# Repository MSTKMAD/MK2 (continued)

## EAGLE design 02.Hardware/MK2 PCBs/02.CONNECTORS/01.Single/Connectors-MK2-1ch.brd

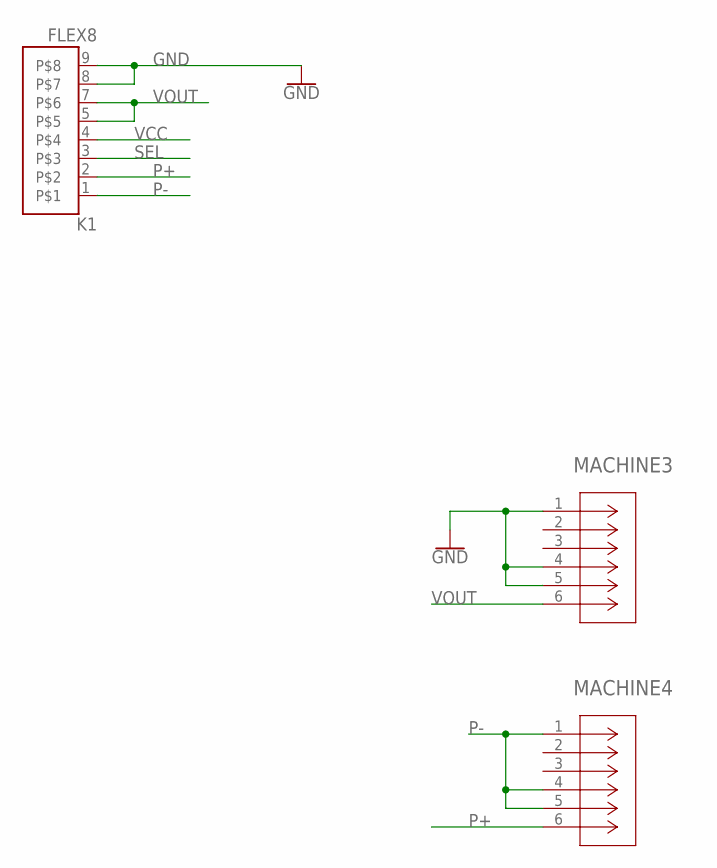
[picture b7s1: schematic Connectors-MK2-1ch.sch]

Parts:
K1: FLEX8
MACHINE3, MACHINE4: ACJS-MHDR; CONN_MHDR_AMP

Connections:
GND: K1.8, K1.9, MACHINE3.1, MACHINE3.4, MACHINE3.5
P+: K1.2, MACHINE4.6
P-: K1.1, MACHINE4.1, MACHINE4.4, MACHINE4.5
SEL: K1.3
VCC: K1.4
VOUT: K1.5, K1.7, MACHINE3.6

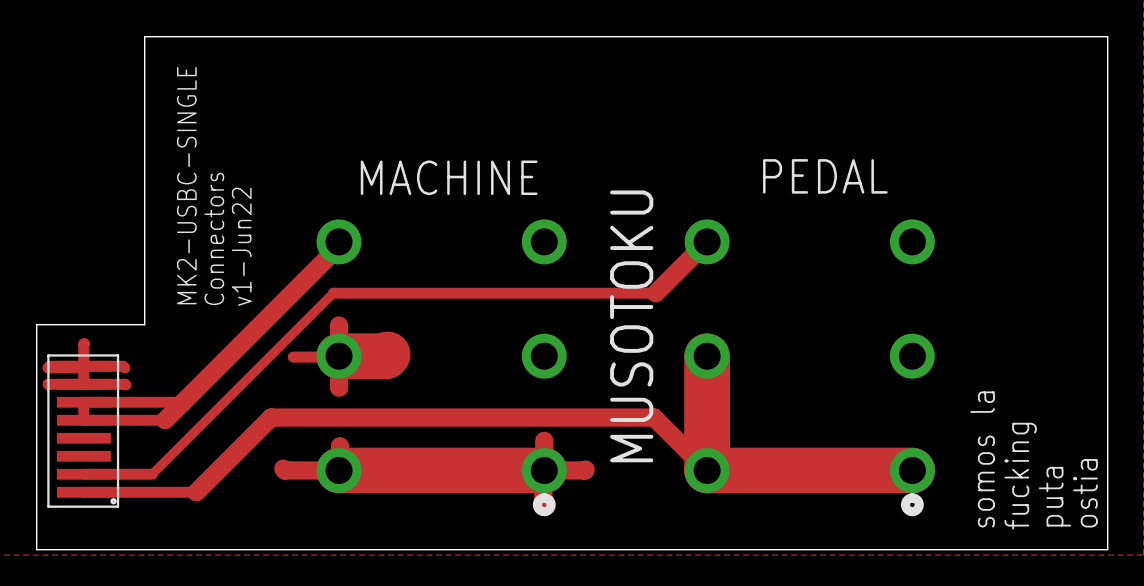
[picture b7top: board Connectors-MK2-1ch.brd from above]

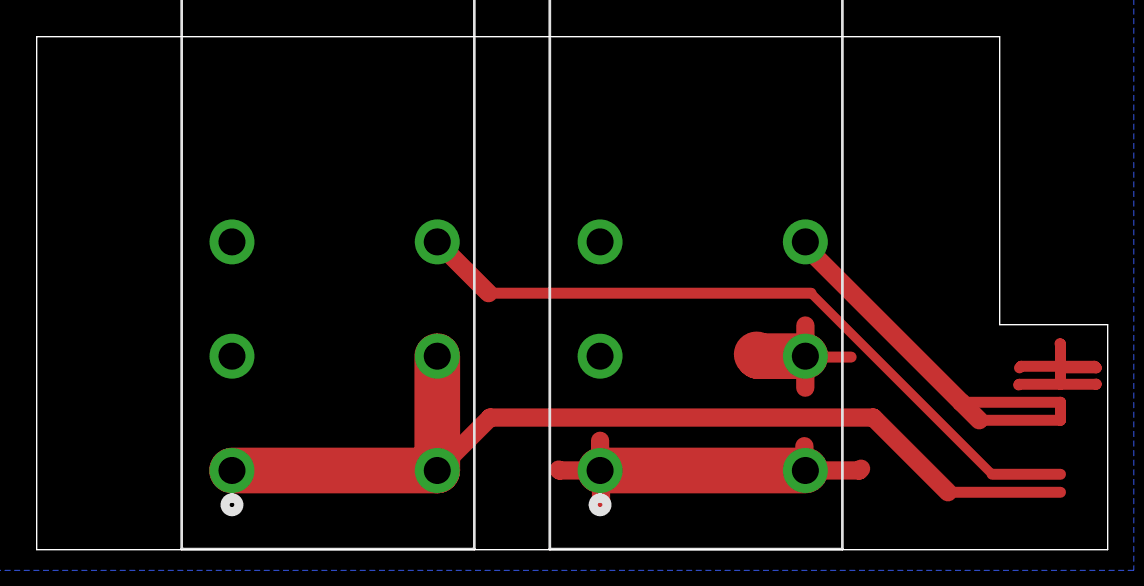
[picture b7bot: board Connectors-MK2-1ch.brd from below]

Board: 2 copper layers, 59.5 x 28.5 mm, 3 parts (2 on the bottom side), 4 nets.

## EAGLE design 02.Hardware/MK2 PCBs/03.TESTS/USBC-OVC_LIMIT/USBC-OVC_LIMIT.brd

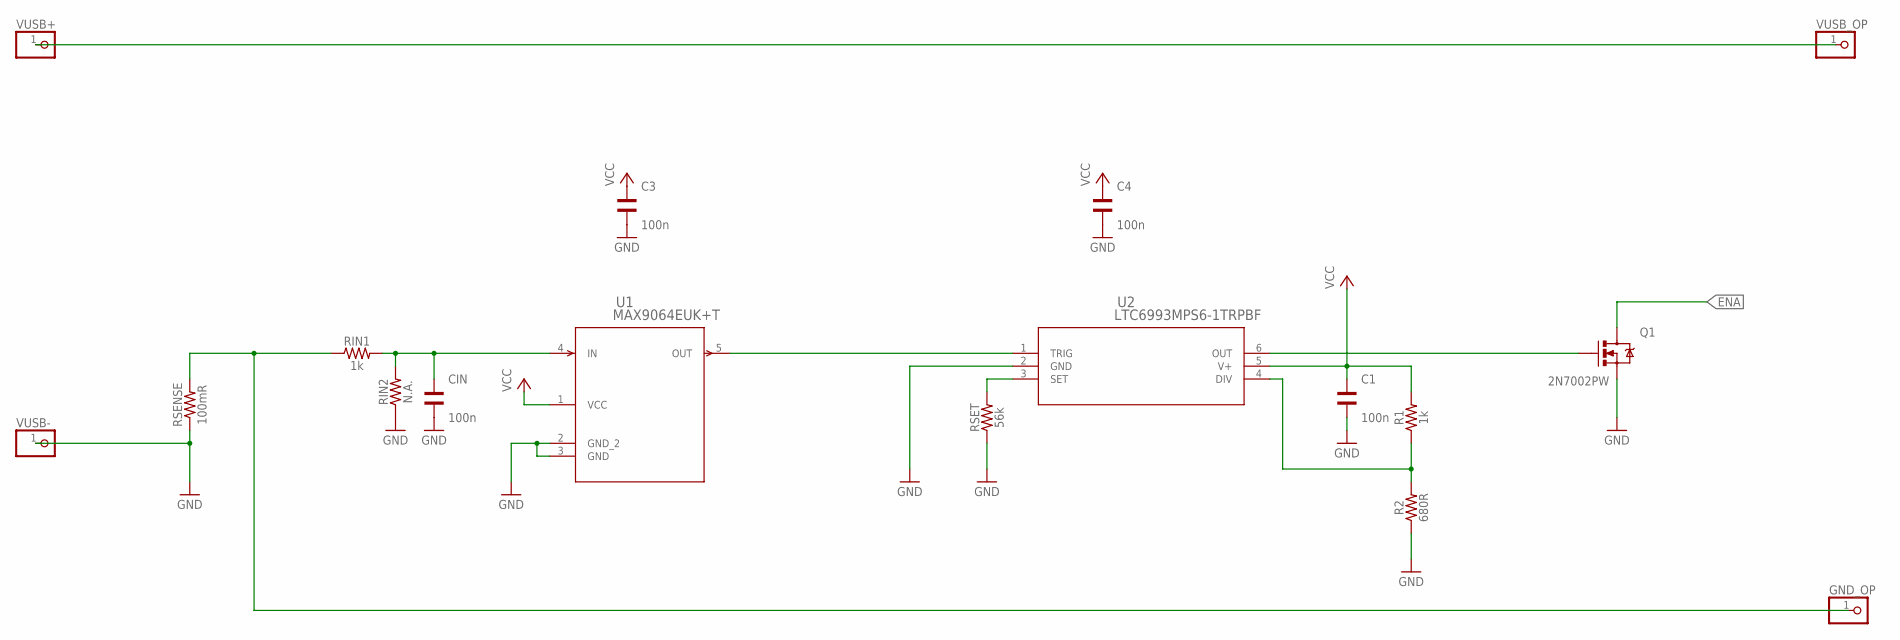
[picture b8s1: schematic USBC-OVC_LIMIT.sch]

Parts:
C1, C3, C4: 100n; WCAP-CSGP_1206
CIN: 100n; WCAP-CSGP_1206
GND_OP: PINHD-1X1; 1X01
Q1: 2N7002PW; SOT323
R1: 1k; 1206
R2: 680R; 1206
RIN1: 1k; 1206
RIN2: N.A.; 1206
RSENSE: 100mR; 1206
RSET: 56k; 1206
U1: MAX9064EUK+T; 21-0057F_MXM
U2: LTC6993MPS6-1TRPBF; TSOT-23_S6_LIT
VUSB+: PINHD-1X1; 1X01
VUSB-: PINHD-1X1; 1X01
VUSB_OP: PINHD-1X1; 1X01

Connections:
ENA: Q1.3 (D)
GND: C1.1, C3.1, C4.1, CIN.1, Q1.2 (S), R2.1, RIN2.1, RSENSE.1, RSET.1, U1.2 (GND_2), U1.3 (GND), U2.2 (GND), VUSB-.1
GND_OP: GND_OP.1, RIN1.1, RSENSE.2
unnamed: RSET.2, U2.3 (SET)
unnamed: CIN.2, RIN1.2, RIN2.2, U1.4 (IN)
unnamed: R1.1, R2.2, U2.4 (DIV)
unnamed: Q1.1 (G), U2.6 (OUT)
unnamed: U1.5 (OUT), U2.1 (TRIG)
VCC: C1.2, C3.2, C4.2, R1.2, U1.1 (VCC), U2.5 (V+)
VUSB_OP: VUSB+.1, VUSB_OP.1

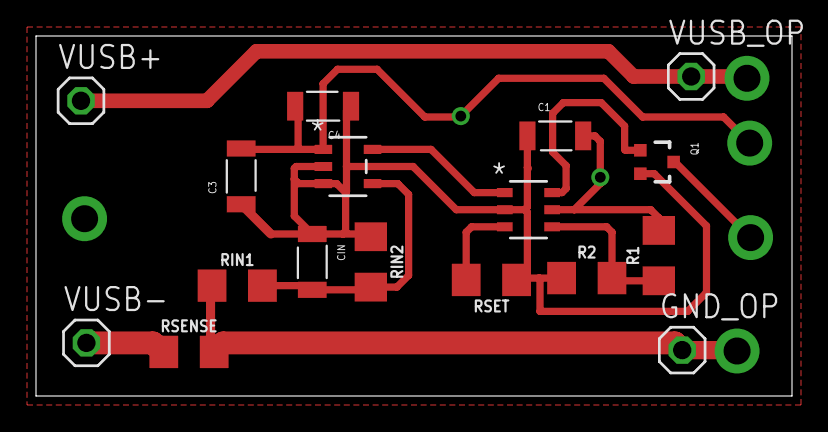
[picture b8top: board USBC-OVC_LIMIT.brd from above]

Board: 2 copper layers, 42.0 x 20.0 mm, 17 parts (0 on the bottom side), 9 nets.

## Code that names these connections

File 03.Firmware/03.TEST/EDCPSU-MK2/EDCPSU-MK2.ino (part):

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const int OVC_UVOLT_MAX_TIME = 1000;          // Maximum time that can last the overcurrent with the UNDERVOLTAGE method (Milliseconds)
const unsigned int OVC_SENSE_LIMIT_INF = 760; // Current limit above which it is still considered an overcurrent sense situation 2.6A
const unsigned int OVC_SENSE_LIMIT_SUP = 800; // Current limit above which it is Triggered the overcurrent sense situation 2.7A real (in theory this value should trigger at 3.1A but Rsense is contaminated by a trace track to the amplifier)
const byte MAX_OVC_ERRORS = 5;                // Max number of OVC errors per session in order to request the release of the PEDAL to the user
const int UNDERVOLT_1V5 = 100;                // Sensed voltage corresponding to 2V for undervoltage sensing
const int UNDERVOLT_1V8 = 121;                // Sensed voltage corresponding to 1.8V for undervoltage sensing
const float DISP_TO_VTARGET_CONV = 5.2;       // Conversion factor to get display values into same scale as VoutSense values (1/19.6)*1023 = 52.2 --> to DISP 52/10=5.2
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const unsigned long RX_CHAR_TIMEOUT = 10; // (ms) time allowed for an orphan char received via Serial
const byte TLG_RX_BYTES = 3;              // Bytes compounding a Serial telegram of the Test mode

const byte ALARM_FLAG = 0; // Flag to report that OVC_ALARM sensor is activated. This is set in ReportFlags report byte in the Test Mode
const byte PEDAL_FLAG = 1; // Flag to report that PEDAL input is activated. This is set in ReportFlags report byte in the Test Mode
// ------------------------------------------------- PIN DEFINITION r7,r6 -------------------------------------------
const int DCDC_EN = A1; //
//const int LED_FRONT = 9; // Arduino 7 (pin 11 in ATMEGA368)
const int LIFE_CHECK = 9; // SPARE2 Pin used for testing

const int ISEN = A7;
const int VOSEN = A6;
const int PUSHBUTTON_IP = A2; // HIGH = OFF; LOW = ON
const int ROTPUSH_IP = A3;    // HIGH = OFF; LOW = ON
const int ROTA = 4;
const int OVC_ALARM = 5; // New in r8.0 (before pin 2)
const int ROTB = 3;
const int BUZZ = 6;
const int PEDAL_IP = 2;    // New in r8.0 (before pin 5)
const int VBUS_SENSE = A0; // New in r8.0 (before LED)
const int CHANNEL_SEL = 7; // Previous HW version this pin was CHG_POL
//const int ENA_OUT = 1;       // TXo-- caution! this digital line overlaps with TXo, so Serial has to be disabled

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int NitroForContinuousMode;               // This varible enables the "RISE event" of the continuous mode and therefore facilitates the Nitro
unsigned long PartialRuntimer = 0;        // Runtimer counter that accounts for the current segment of time being added up to the total counter.
// Each time that it is around 1 minute accumulated, it is transferred to the TotalRuntimer and the PartialRuntimer is cleared.
unsigned long TotalRuntimer = 0; // Accounts for the total run time of this session
byte RuntimerEnable = true;      // Variable used for getting noticed for Runtimer to run.
int runningHours;                // Used by Runtimer
int runningMinutes;              // Used by Runtimer
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unsigned long ShowLongPressTimer;           // Timer to control the longpress information shown on display (Milliseconds)
byte ShowLongpressInfo = NO_LONGPRESS_INFO; // ATTENTION: Global var! Determines if Longpress info has to be shown. Used on other display
// functions to enable or not the display info.
byte OVCerrorsConsecutive = 0; // Number of consecutive OVC errors. After reached a limit, it is requiered that pedal is released by user in order to continue

byte RxBuffer;                  // Number of bytes received at Serial
unsigned long TimedataInBuffer; // Timer for Serial reception in Test Mode
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  //  digitalWrite(LED_FRONT, LOW);
  //  pinMode(LED_FRONT, OUTPUT);
  pinMode(LIFE_CHECK, OUTPUT);
  pinMode(VBUS_SENSE, INPUT);
  pinMode(PUSHBUTTON_IP, INPUT);
  pinMode(ROTPUSH_IP, INPUT);
  pinMode(ROTA, INPUT);
  pinMode(ROTB, INPUT);
  pinMode(BUZZ, OUTPUT);
  pinMode(PEDAL_IP, INPUT);
  pinMode(ISEN, INPUT);
  pinMode(VOSEN, INPUT);
  pinMode(DCDC_EN, OUTPUT);

  //  pinMode(ENA_OUT, OUTPUT);
  pinMode(CHANNEL_SEL, OUTPUT);
  pinMode(OVC_ALARM, INPUT);

  //-----------------

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      }
    }

    //--Performs Spin Action depending on Run Mode--
    if (RotaryDebounced == true)
    {
      EncoderChangePrev = EncoderChange; // EncoderChangePrev is ONLY updated once the spin direction change is consolidated
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
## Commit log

2022-05-23 WIP EDCPSU r1 (Ready To Revision)
2022-05-23 Revision de version definitva Javi
2022-05-23 Update Note 22-RTR (Ready To Revision)
    Add Resistor N.A for Divisor
    Connect USb Shield to GND
    Fix silkcreen and Position
    Fix IN_OVC to MCPU
    Plane for VOUT and GND in Flex Connection
    Fix Test Pint Positions
2022-05-23 Create PCB Connectors-MK2
2022-05-23 Añadido SPARE2 + revisión
    Se añade SPARE2 con R y Pad para tener un punto de acceso al pin 13 de CPU.
    Pequeños cambios en revisión
2022-05-24 Pequeños cambios ruteado
2022-05-24 Create BOM Mk2
2022-05-25 Update EDCPSUMK2.brd
    Solucion a la estrangulacion del plano de Vcc(19v) en la capa PWR en la parte superiror izquierda.
2022-05-26 Planos modificados
2022-05-26 Update PCB ECPSUMK2
    Actualizacion y mejora de las capas de PWR y GND
2022-05-26 Se actualiza Titulo (cajetin) a MK2 r1 mayo 22
2022-05-27 Delete MK2_BOM.xlsx
    Se mueve de sitio y cambia de nombre
2022-05-27 Doc fabricacion SETI
    Primer envío a SETI
2022-05-27 Migrado desde el documento DOC de Javi
2022-05-27 Convertido a EXCEL
2022-05-27 Convertido de documento WORD de Javi
2022-05-27 Varios cambios
    Se separa de la tarjeta de conectores
    Se añade indicación en el histórico de procedencia
    Se corrige alguna linea que sí monta SETI
2022-05-27 Creacion
2022-05-27 Gerbers
2022-05-30 Create PCB CONECTOR_MK2_SINGLE
2022-06-13 Se añade la FAJA de poliester
2022-06-15 Flex MK2 Creation
2022-06-15 MK1 connector
2022-06-16 Cleanup trazado + GERBERs
    Versión de primera compra a PCBWAY
2022-06-17 Cambio Grosor y Carpetas nuevas
    Se cambia el grosor de las pistas de VOUT y la conexión a las vías de los conectores.
    ----------
    Creación de las carpetas dentro de la
2022-08-05 Pruebas mecanicas en EDCPSUr16
2022-08-05 Placa de prueba de control de overcurrent
2022-08-05 Ficheros de referencia version 731 de la Machete MK1
2022-08-05 Ficheros referencia version 730 Dual
2022-08-05 Documentacion conectores de la MK2 Dual
2022-08-05 Ficheros Lentilla Led Frontal MK2
2022-08-05 Creacion BOM Conectores y EDCPSU MK2
2022-08-05 Creacion Main code MK2 Dual
2022-08-05 Create Note 11 May 2023.pdf
    Diseño esquematico electronica adicional en EDCPSU y placa conectores MK2 dual
2022-08-10 Inserccion del nuevo icono y actualizacion del nitro
2022-08-10 PCB 1channel - CAM output generado
2022-08-16 Inclusion de Librerias
    Adafruit_BusIO
    Adafruit GFX
    Adafruit SSD1306
    SOFTI2CMaster
2022-08-16 Update Code
2022-08-16 Cierre de Issue #3. Cambios menores
    #3- https://www.notion.so/Arranque-de-la-M2-muestra-el-logo-durante-muy-poco-tiempo-Antes-3s-ahora-1s-f0cdef7c8bc9491a815bdf0ef47de030
    Se cambia la duracion del LongPress de 800 a 900 para prevenir el encendido NO intencionado. (Testing)
    Cambio en la nomnclatura a MK2-DUAL
2022-08-17 Close Issue #4,#5,#6.
    #4 Se decide cambiar el texto que se muestra. Se vuelva a mostras el encendido y apagado del modo continuo independientemente del canal.
    #5 Se coloca la Palabra NITRO en la esquina inferior izquierda siempre que el nitro se encuentre activado.
    #6 En la activación del pulsador se realiza una comprobación de si el pedal esta activo o no. En caso afirmativo no se permite el cambio de canal.
2022-08-17 Release Candidate MK2-Dual version801
2022-08-19 Create EDCPSU-MK2-DUAL.ino.hex Release Candidate v801
2022-08-29 Updata EDCPSU-MK2-DUAL.ino. Independencia por canal del modo Nitro
    Independencia de la activacion Nitro por canal.
    Almacenamiento en EEPROM del estado de cada canal de la Configuracion del Nitro
    Issue #7:
    https://www.notion.so/Activaci-n-independiente-del-Nitro-para-cada-Canal-Almacenamiento-en-EEPROM-2c2c8b672f0b42c3aefab32c016fb566
2022-08-30 Release Candidate v802. Close Issue #7
    Creacion constantes para los canales mejora Coding Standar.
2022-08-30 Creacion v802 .HEX
2022-09-28 v803 Detección de un cargador USB-C no compatible
    Se incluye una lectura de la tension de entra mientras se muestra el Logo.
    Si la tension de entrada esta por debajo de 17,5v se considera que no es compatible.
    A partir de 16v el DCDC tienen una caida de 2v a 16 voltios en la tension de salida.
2022-11-07 Informacion de pedido para PCBWAY
2022-11-24 v804.Cierre del Issue #8. y creacion carpeta con ficheros HEX
2022-11-30 Cambio dimension Fajas. Cierre Issue #9
2022-11-30 Creacion Gerber
    Se corrige la serigrafia a V2.
2023-01-19 update gitignore
2023-02-03 Creacion y Ajuste de faja para Single output a raiz de la v2 de la faja para dual output.
2023-02-03 Revision de la creacion de la nueva faja
    Se cambia DRC a 10mil para todo el diseño
    Se corrigen fallos de clearance
2023-02-10 Close #1
2023-02-10 Program File .hex Version 805
2023-02-24 Se actualiza el como pedir la faja a PCBWAY
    Ahora 0.13mm en vez de 0.25mm
2023-03-07 Cierra issuel #2
    referencia de conector nueva: ACJS-MHOM
2023-03-07 Cierra la issue #3
2023-03-10 Creacion de carpeta rp2040, documentacion sobre la rasp picp y el rp2040. Archivo de pcb con los primeros cambios.
2023-03-14 Propuesta 1 MK2 2040
2023-03-22 Version de comienzo de rediseño
2023-03-23 Adapatacion cambios MK2 RP2040
2023-03-23 correccion esquamtico
2023-03-24 1º Colocacion de componentes en el brd
2023-03-26 Pequeños cambios
2023-03-27 Continuacion de cambios. Rutado inicial de todos los componentes. Falta asignacion de pines.
2023-03-27 Pequeñas modificaciones
2023-03-28 Propuesta de routeado 1
2023-03-29 Propuesta de routeado 2
2023-04-01 Cambios menores antes de pedir a PCBWAY
2023-04-04 Migracion y adaptacion de librerias a la version rp2040
2023-04-04 Bom V1
2023-04-04 Añadido Test Pads
2023-05-02 Version 1 de la pogo test de la MK2-RP2040
2023-05-02 Correcion errores
2023-05-02 PCB que servra de calzador para la pogo pin
2023-05-09 Prototipo 1 - PCBWAY 9 MAY - SETI
2023-05-12 BOM adelanto SETI
2023-05-16 Placa de testeo de cargadores Tipo C
2023-05-16 Pedido a PCBWAY (ultimas modificaciones)
    Revision del diseño de Javi
    Se añade landing mas largo para el opto
2023-05-16 Revision antes de enviar a SETI
    Se corrigen varios links
    Se crea columna de selección para fabricacion de DUAL USBC o MK1 y asi ajustar la producción
2023-05-30 Version 2 revisada de la EDCPSU
    Los cambios son referidos a los issues #5, #6, #7, #8, #9, #10, #11, #12.
2023-05-31 v3 BOM. cambios para seti
    Columna de cambios.
2023-05-31 Actualizacion de Cambios menores
    R15 con valor 0R.
    Lineas de Ref de tension a 3V_REF y R57 ajustada a 330R #10
    Aumento de la linea de potencia de GND en la zona de la faja.
    Mejora del marcaje de la colocacion de los Diodos.
2023-05-31 Update EDCPSUMK2-RP2040
    Cambio del Zener del 3,6v a 3,9v. #13
2023-06-01 Update EDCPSUMK2-RP2040 - Diodo entrada D1
    Cambio del diodo D1 de bidireccional a Unidireccional de 24v. #14
2023-06-01 Produccion SETI - Modificaciones menores y generacion de GERBER para fabricacion
2023-06-06 Adapatacion para compatibilidad con la libreria EEPROM de RP2040
2023-06-06 Adaptacion de pines del integrado final
2023-06-06 Adaptacion del ADC de 10 a 12 bits.
2023-06-14 Fallo en el I2C. #Issue 15
2023-08-10 Close #16
2023-08-10 Limpieza de Codigo
    Lineas que son para debug/desarrollo o espacios que se ha suprimido para mejorar la legibilidad-
2023-08-10 Ajuste de los valores del sensado de entrada
2023-08-10 Carpetas para compilacion y testeo
2023-08-11 Documento validacion de MKx-RP2040
    OJO Faltan las fotos
2023-08-11 Fotos añadidas
2023-09-08 Tarjeta de Testeo MK2040 v1
    Pendiente de Revision
2023-09-08 Charge Tester Software
2023-09-08 Fix fecha de creacion
2023-09-11 Fix errors.
    Cooper clereance 6mil ->8mil.
    Isolate de los planos a 0,254 mils.
    DRC aproved
2023-09-11 Librerias Eagle.
2023-10-11 Issue #18
    Version 1 de la propuesta de cambio
2023-10-30 Revision de PCB (DGB)
2023-10-30 Correccion Errores
    Señal Vcc sin conectar.
    Añadido sensado de señales VBUS_SENSE y OVC_ALARM.
    Mejorado el Plano de GND para evitar estrangulamientos.
    Ensanchadas las pistas que conectan con vias.
2023-11-22 Cambio de R7
    El valor se cambia para tener en cuenta la R1 presente en la tarjeta cuando la señal OVC_ALARM es activada y prevenir la raspi de una subida de tension en la entrada digital.
2023-11-22 Actualizacion Gitignore
    Se deja de trackear la carpeta de .build
2023-12-14 Formating version Ardunio
2023-12-14 Actualizacion Nitro
    Se amplian los escalones de la escalera ascendente del NITRO para que alcance los 200ms de subida.
2023-12-14 Ajuste de la proteccion de corto circuito
2023-12-14 Formating version RP2040
2024-02-05 Correccion de la version en pagina principal. No hay cambios de valores
2024-05-27 Creacion del excel de control de sistema
2024-05-27 RESET
2024-11-13 Tester rp2040
2024-11-13 Cambios menores de programacion
2024-11-13 Actualizacion v806
2025-02-10 Temporizador de vida
2026-01-16 Finish Doc
